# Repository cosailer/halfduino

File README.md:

# halfduino
this is an arduino clone with half width and height

**specification:**\
mcu: atmega32l\
usb-serial:ch340e\
width:34.29mm\
height:26.67mm

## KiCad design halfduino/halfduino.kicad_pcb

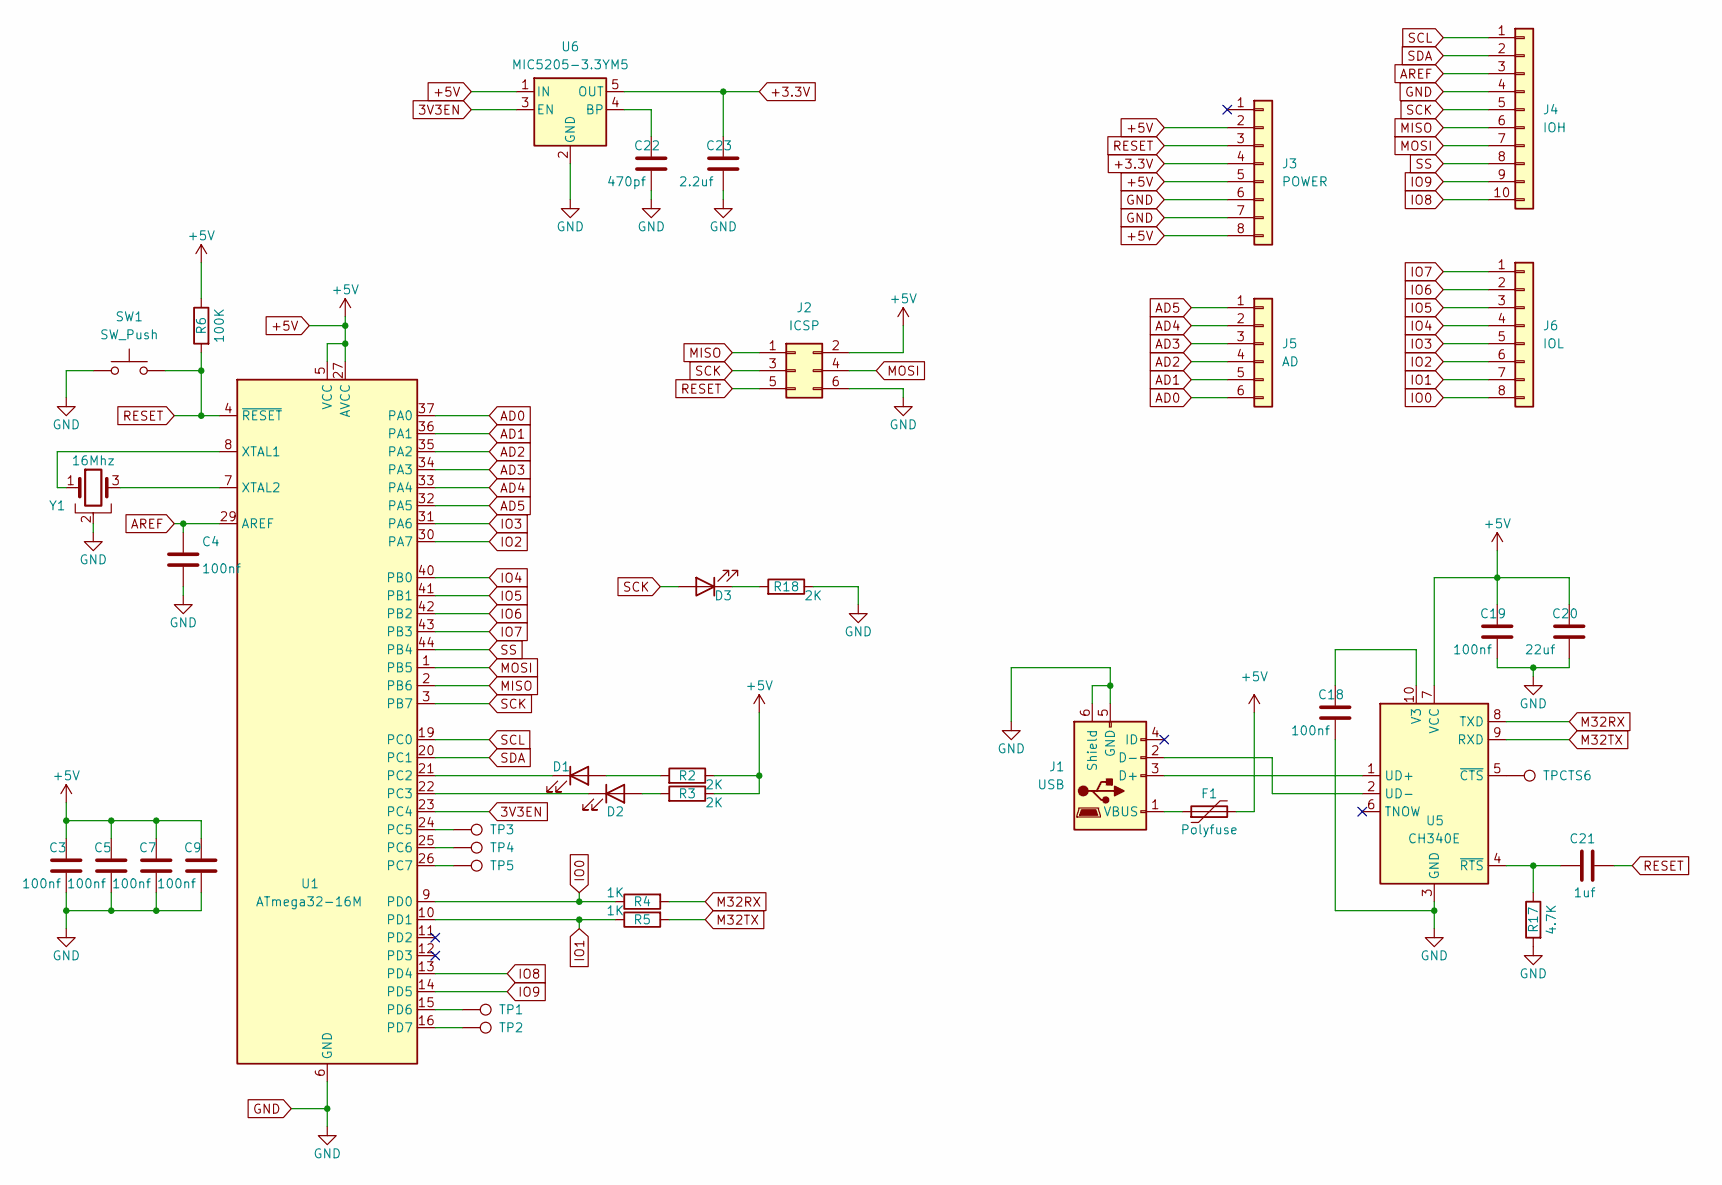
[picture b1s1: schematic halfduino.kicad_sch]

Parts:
C3, C4, C5, C7, C9, C18, C19: 100nf; C_0603_1608Metric_Pad1.08x0.95mm_HandSolder
C20: 22uf; C_0603_1608Metric_Pad1.08x0.95mm_HandSolder
C21: 1uf; C_0603_1608Metric_Pad1.08x0.95mm_HandSolder
C22: 470pf; C_0603_1608Metric_Pad1.08x0.95mm_HandSolder
C23: 2.2uf; C_0603_1608Metric_Pad1.08x0.95mm_HandSolder
D1, D2, D3: LED; LED_0603_1608Metric_Pad1.05x0.95mm_HandSolder
F1: Polyfuse; Fuse_1206_3216Metric
J1: USB; USB_Micro-B_Wuerth_629105150521
J2: ICSP; PinHeader_2x03_P1.27mm_Vertical
J3: POWER; PinHeader_1x08_P1.27mm_Vertical
J4: IOH; PinHeader_1x10_P1.27mm_Vertical
J5: AD; PinHeader_1x06_P1.27mm_Vertical
J6: IOL; PinHeader_1x08_P1.27mm_Vertical
R2, R3, R18: 2K; R_0603_1608Metric_Pad0.98x0.95mm_HandSolder
R4, R5: 1K; R_0603_1608Metric_Pad0.98x0.95mm_HandSolder
R6: 100K; R_0603_1608Metric_Pad0.98x0.95mm_HandSolder
R17: 4.7K; R_0603_1608Metric_Pad0.98x0.95mm_HandSolder
SW1: SW_Push; SW_Push_1P1T_NO_Vertical_Wuerth_434133025816
TP1, TP2, TP3, TP4, TP5: TestPoint; TestPoint_Pad_D1.0mm
TPCTS6: TestPoint; TestPoint_Pad_D1.0mm
U1: ATmega32-16M; QFN-44-1EP_7x7mm_P0.5mm_EP5.15x5.15mm_no_pad
U5: CH340E; MSOP-10_3x3mm_P0.5mm
U6: MIC5205-3.3YM5; SOT-23-5
Y1: 16Mhz; Resonator_SMD_Murata_CSTxExxV-3Pin_3.0x1.1mm

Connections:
3V3EN: U1.23 (PC4), U6.3 (EN)
+3.3V: C23.1, J3.4, U6.5 (OUT)
+5V: C3.1, C5.1, C7.1, C9.1, C19.1, C20.1, F1.2, J2.2, J3.2, J3.5, J3.8, R2.1, R3.1, R6.1, U1.5 (VCC), U1.17 (VCC), U1.27 (AVCC), U1.38 (VCC), U5.7 (VCC), U6.1 (IN)
AD0: J5.6, U1.37 (PA0)
AD1: J5.5, U1.36 (PA1)
AD2: J5.4, U1.35 (PA2)
AD3: J5.3, U1.34 (PA3)
AD4: J5.2, U1.33 (PA4)
AD5: J5.1, U1.32 (PA5)
AREF: C4.1, J4.3, U1.29 (AREF)
GND: C3.2, C4.2, C5.2, C7.2, C9.2, C18.2, C19.2, C20.2, C22.2, C23.2, J1.5 (GND), J1.6 (Shield), J2.6, J3.6, J3.7, J4.4, R17.2, R18.1, SW1.1, U1.6 (GND), U1.18 (GND), U1.28 (GND), U1.39 (GND), U5.3 (GND), U6.2 (GND), Y1.2
IO0: J6.8, R4.1, U1.9 (PD0)
IO1: J6.7, R5.1, U1.10 (PD1)
IO2: J6.6, U1.30 (PA7)
IO3: J6.5, U1.31 (PA6)
IO4: J6.4, U1.40 (PB0)
IO5: J6.3, U1.41 (PB1)
IO6: J6.2, U1.42 (PB2)
IO7: J6.1, U1.43 (PB3)
IO8: J4.10, U1.13 (PD4)
IO9: J4.9, U1.14 (PD5)
M32RX: R4.2, U5.8 (TXD)
M32TX: R5.2, U5.9 (RXD)
MISO: J2.1, J4.6, U1.2 (PB6)
MOSI: J2.4, J4.7, U1.1 (PB5)
unnamed: D1.2 (A), R2.2
unnamed: D1.1 (K), U1.21 (PC2)
unnamed: D2.2 (A), R3.2
unnamed: D2.1 (K), U1.22 (PC3)
unnamed: D3.1 (K), R18.2
unnamed: J1.3 (D+), U5.1 (UD+)
unnamed: J1.2 (D-), U5.2 (UD-)
unnamed: F1.1, J1.1 (VBUS)
unnamed: TP3.1, U1.24 (PC5)
unnamed: TP4.1, U1.25 (PC6)
unnamed: TP5.1, U1.26 (PC7)
unnamed: TP1.1, U1.15 (PD6)
unnamed: TP2.1, U1.16 (PD7)
unnamed: U1.8 (XTAL1), Y1.1
unnamed: U1.7 (XTAL2), Y1.3
unnamed: C18.1, U5.10 (V3)
unnamed: TPCTS6.1, U5.5 (~CTS)
unnamed: C21.1, R17.1, U5.4 (~RTS)
unnamed: C22.1, U6.4 (BP)
RESET: C21.2, J2.5, J3.3, R6.2, SW1.2, U1.4 (~RESET)
SCK: D3.2 (A), J2.3, J4.5, U1.3 (PB7)
SCL: J4.1, U1.19 (PC0)
SDA: J4.2, U1.20 (PC1)
SS: J4.8, U1.44 (PB4)

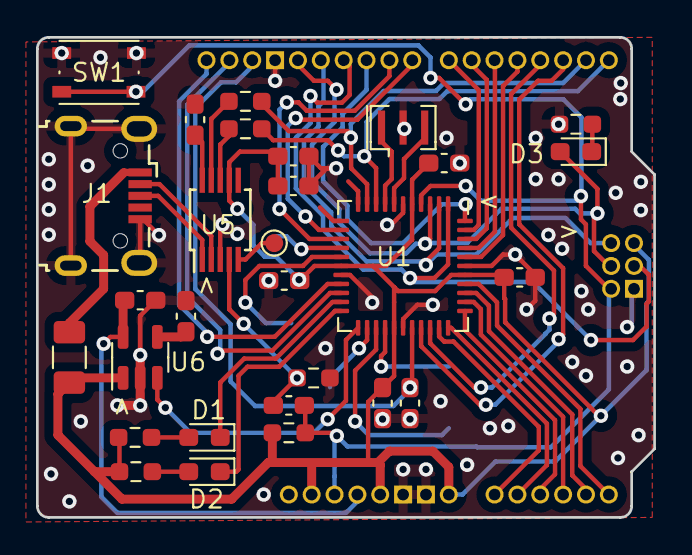
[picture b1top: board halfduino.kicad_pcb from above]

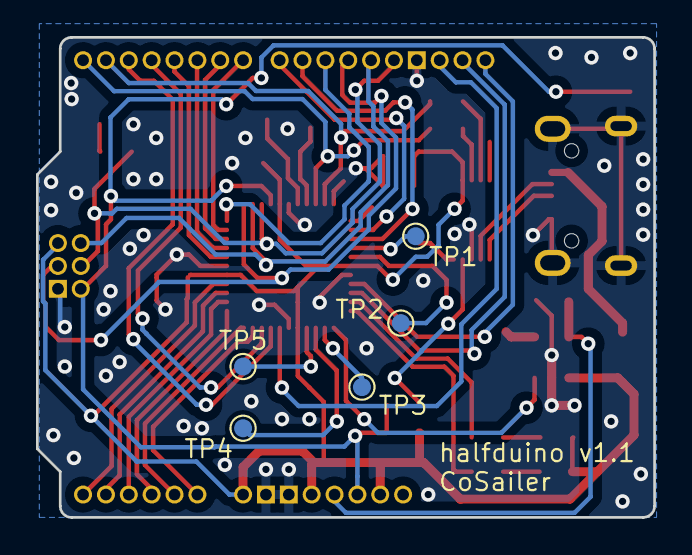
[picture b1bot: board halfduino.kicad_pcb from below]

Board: 2 copper layers, 34.3 x 26.7 mm, 39 parts (5 on the bottom side), 49 nets.

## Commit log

2023-10-21 add hardware v1.1
    add hardware v1.1
